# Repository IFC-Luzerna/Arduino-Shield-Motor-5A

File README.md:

# Arduino Shield Motor 5A
<div style="display: inline_block">

</div>

Shield de Arduino Uno para controle de motor de corrente contínua.

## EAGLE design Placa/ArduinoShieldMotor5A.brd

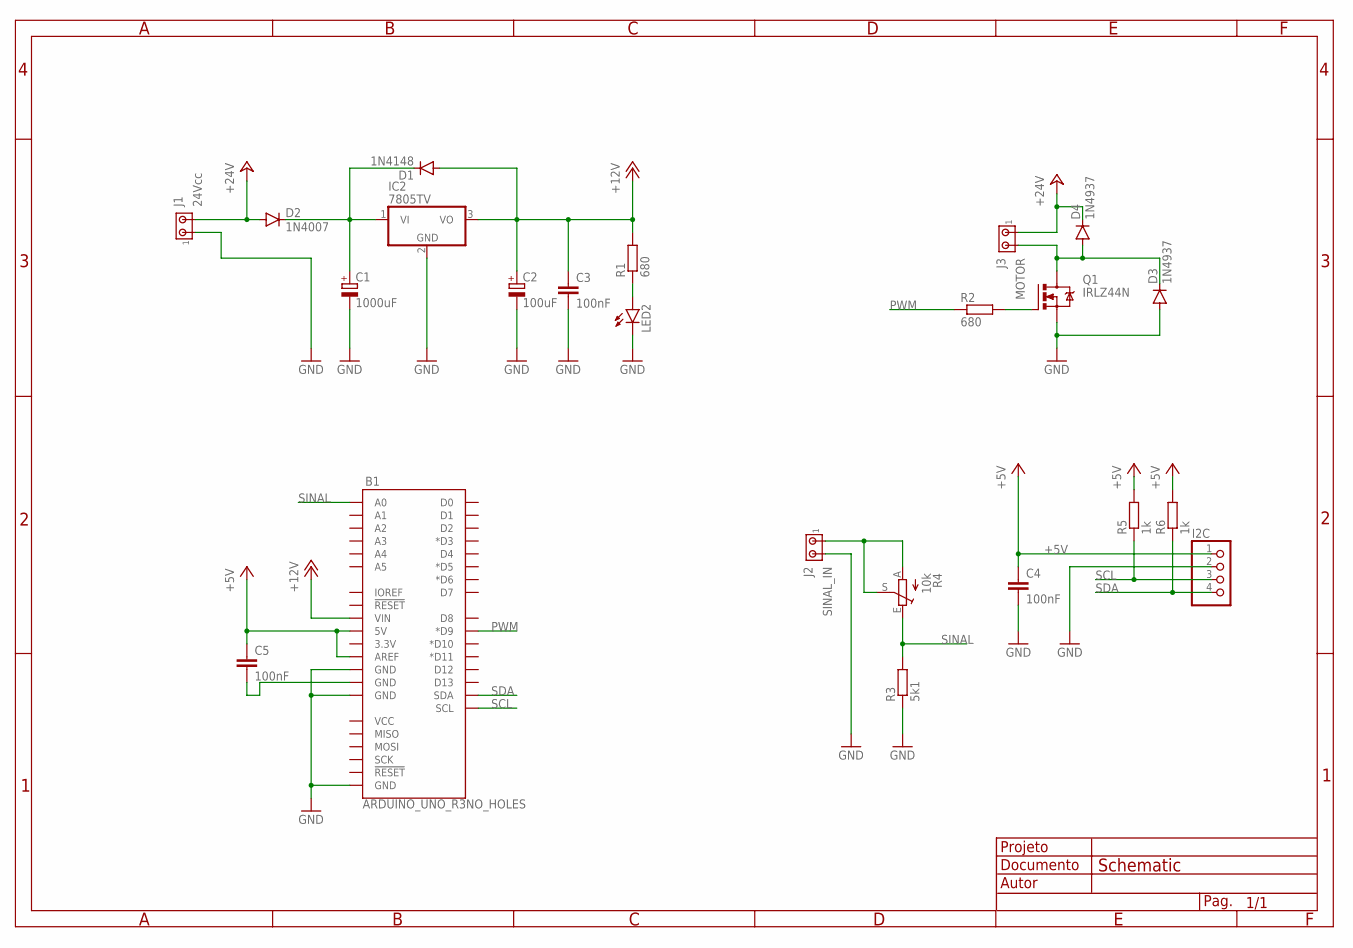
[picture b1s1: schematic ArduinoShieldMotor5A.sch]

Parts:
B1: ARDUINO_UNO_R3NO_HOLES; ARDUINO_R3_NO_HOLES
C1: 1000uF; E5-13
C2: 100uF; E2,5-5
C3, C4, C5: 100nF; C025-025X050
D1: 1N4148; DO35-10
D2: 1N4007; DO41-10
D3, D4: 1N4937; DO41-10
I2C: PINHD-1X4; 1X04
IC2: 7805TV; TO220V
J1: 24Vcc; 1X2MTA
J2: SINAL_IN; 1X2MTA
J3: MOTOR; 1X2MTA
LED2: LED3MM
Q1: IRLZ44N; TO220BV
R1, R2: 680; 0207/10
R3: 5k1; 0207/10
R4: 10k; B64Y
R5, R6: 1k; 0207/10

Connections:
+5V: B1.5V, B1.AREF, C4.1, C5.1, I2C.1, R5.2, R6.2
+12V: B1.VIN, C2.+, C3.1, D1.A, IC2.3 (VO), R1.2
+24V: D2.A, D4.C, J1.2, J3.1
GND: B1.GND@1 (GND), B1.GND@2 (GND), B1.GND@4 (GND), C1.-, C2.-, C3.2, C4.2, D3.A, I2C.2, IC2.2 (GND), J1.1, J2.2, LED2.K (C), Q1.S, R3.1
unnamed: C1.+, D1.C, D2.C, IC2.1 (VI)
unnamed: Q1.G, R2.2
unnamed: LED2.A, R1.1
unnamed: D3.C, D4.A, J3.2, Q1.D
unnamed: B1.GND@3 (GND), C5.2
unnamed: J2.1, R4.A, R4.S
PWM: B1.D9 (*D9), R2.1
SCL: B1.SCL, I2C.3, R5.1
SDA: B1.SDA, I2C.4, R6.1
SINAL: B1.A0, R3.2, R4.E

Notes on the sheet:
Schematic

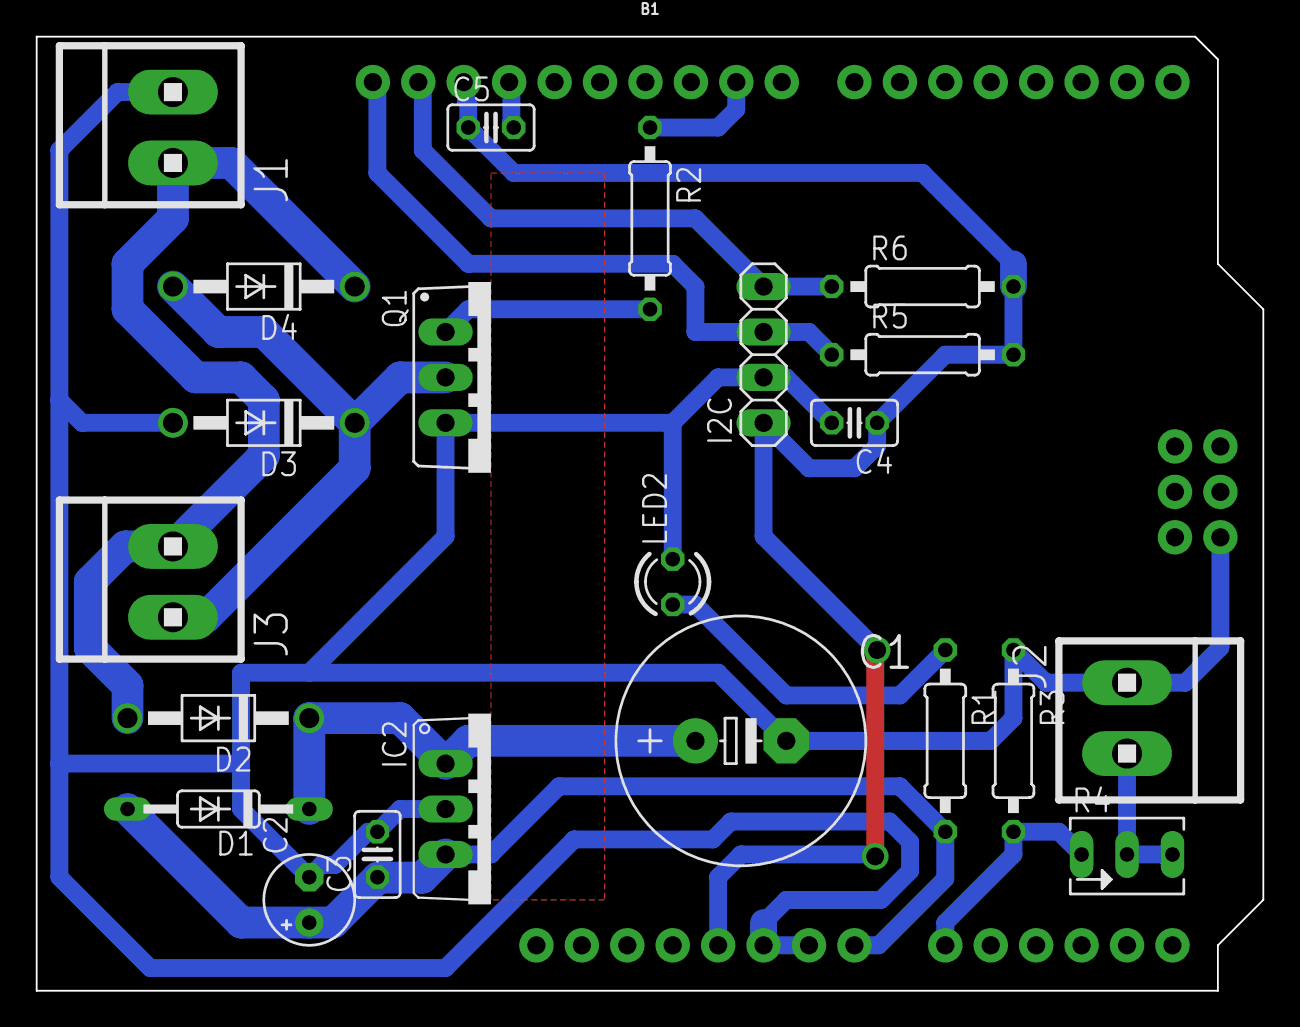
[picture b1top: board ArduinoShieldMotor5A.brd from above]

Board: 2 copper layers, 68.6 x 53.3 mm, 23 parts (0 on the bottom side), 14 nets.

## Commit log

2022-12-08 Placa
    Arquivos do esquemático e do board do projeto
2022-12-08 Update README.md
    Atualização do README

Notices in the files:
parts and their libraries:
SparkFun-Boards: Licensing: Creative Commons ShareAlike 4.0 International - https://creativecommons.org/licenses/by-sa/4.0
